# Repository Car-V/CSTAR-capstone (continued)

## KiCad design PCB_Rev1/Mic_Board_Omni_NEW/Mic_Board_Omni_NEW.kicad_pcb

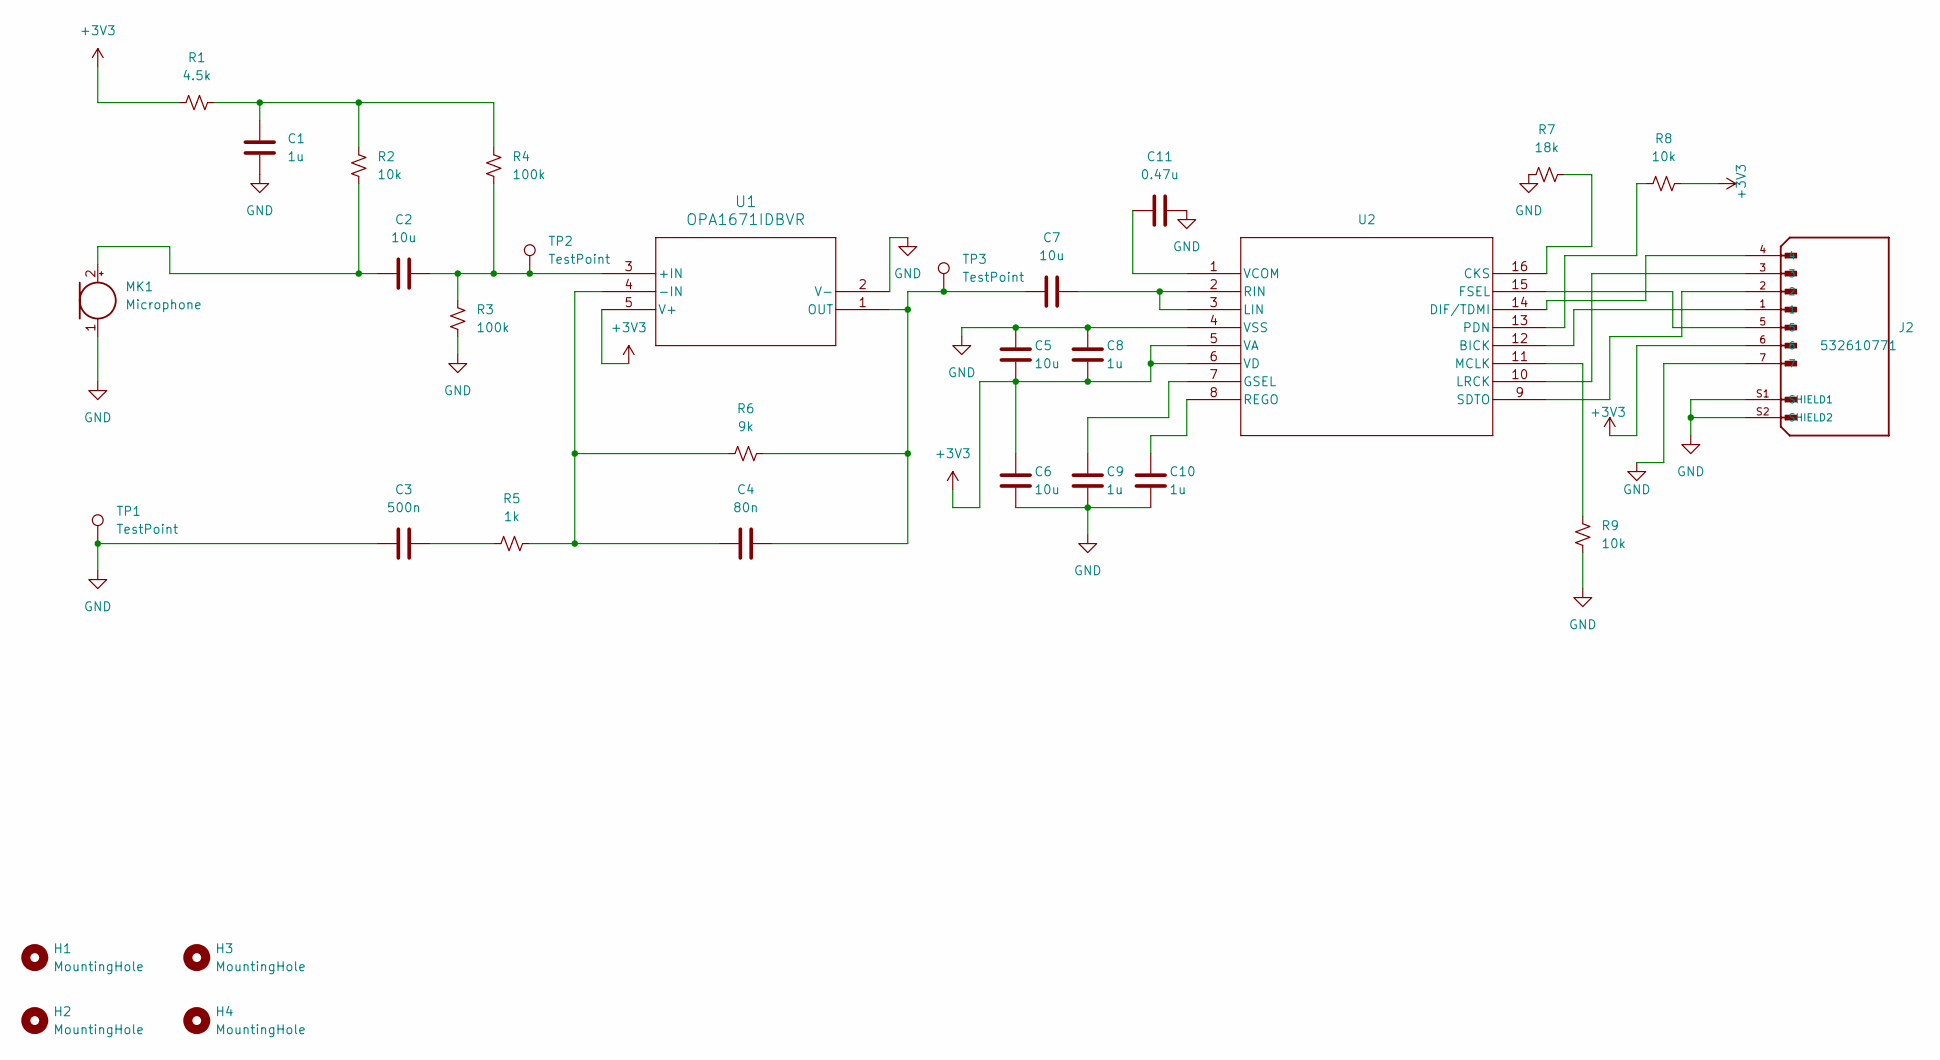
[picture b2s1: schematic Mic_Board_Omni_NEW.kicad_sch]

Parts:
C1, C8, C9, C10: 1u; C_0805_2012Metric; LCSC C519973
C2, C5, C6, C7: 10u; C_0805_2012Metric; LCSC C88484
C3: 500n; C_0805_2012Metric; LCSC C576434
C4: 80n; C_0805_2012Metric; LCSC C3857194
C11: 0.47u; C_0805_2012Metric; LCSC C519977
H1, H2, H3, H4: MountingHole; MountingHole_3.2mm_M3
J2: 532610771; MOLEX_connector; PARTREV J; DigiKey_Part_Number WM7625TR-ND
MK1: Microphone; Omnidirectional; LCSC C3273770
R1: 4.5k; R_0805_2012Metric; LCSC C865529
R2, R8, R9: 10k; R_0805_2012Metric; LCSC C110775
R3, R4: 100k; R_0805_2012Metric; LCSC C96346
R5: 1k; R_0805_2012Metric; LCSC C95781
R6: 9k; R_0805_2012Metric; LCSC C868262
R7: 18k; R_0805_2012Metric; LCSC C137468
TP1, TP2, TP3: TestPoint; TestPoint_Pad_D1.0mm
U1: OPA1671IDBVR; Op-Amp; LCSC C1849409
U2: ADC; LCSC C1519002

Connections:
+3V3: C5.2, C6.1, C8.2, J2.6, R1.2, R8.2, U1.5 (V+), U2.5 (VA), U2.6 (VD)
GND: C1.2, C3.1, C5.1, C6.2, C8.1, C9.2, C10.2, C11.2, H1.1, H2.1, H3.1, H4.1, J2.7, J2.S1 (SHIELD1), J2.S2 (SHIELD2), MK1.1 (-), R3.2, R7.1, R9.1, TP1.1, U1.2 (V-), U2.4 (VSS)
unnamed: C1.1, R1.1, R2.1, R4.1
unnamed: C3.2, R5.2
unnamed: C2.1, MK1.2 (+), R2.2
unnamed: C2.2, R3.1, R4.2, TP2.1, U1.3 (+IN)
unnamed: C4.1, R5.1, R6.2, U1.4 (-IN)
unnamed: C4.2, C7.1, R6.1, TP3.1, U1.1 (OUT)
unnamed: J2.1, U2.12 (BICK)
unnamed: R7.2, U2.16 (CKS)
unnamed: J2.4, U2.14 (DIF/TDMI)
unnamed: J2.5, U2.15 (FSEL)
unnamed: C9.1, U2.7 (GSEL)
unnamed: C7.2, U2.2 (RIN), U2.3 (LIN)
unnamed: J2.3, U2.10 (LRCK)
unnamed: R9.2, U2.11 (MCLK)
unnamed: R8.1, U2.13 (PDN)
unnamed: C10.1, U2.8 (REGO)
unnamed: J2.2, U2.9 (SDTO)
unnamed: C11.1, U2.1 (VCOM)

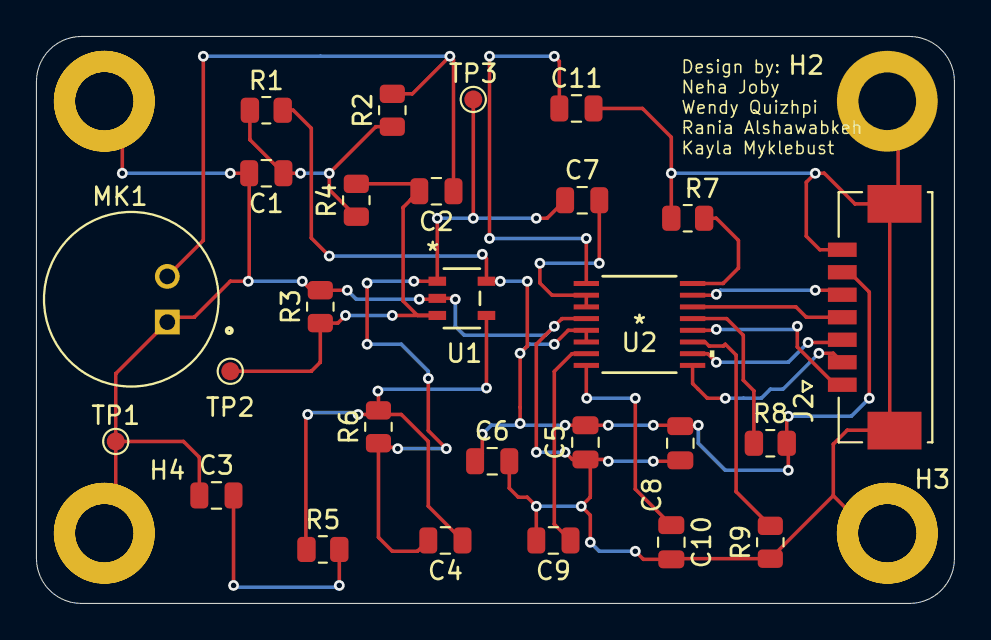
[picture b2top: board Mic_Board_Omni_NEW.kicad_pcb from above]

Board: 2 copper layers, 51.0 x 31.5 mm, 31 parts (0 on the bottom side), 20 nets.

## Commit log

2025-01-11 Add lifecycle_node package
2025-01-11 Moved test node to example sub_folder
2025-01-11 Add Subsystem Nodes
2025-01-11 Rename Folders
2025-01-11 Basic Object Oriented Setup
    This is super basic and I didn't put too much time into all the classes and stuff, will def need more and to iron out the purposes of each class. Lets discuss!
2025-01-12 Moving to CSTAR capstone
2025-01-12 Motor Driver
    Motor driver, encoder connections, and motor connections
2025-01-12 Wendy's Mic schem changes
2025-01-12 Both Mic Board 1 and Mic Board 2 were created + updated
2025-01-13 MicBoard Added to MainBoard
2025-01-14 Setup Software Layout
2025-01-14 Update Name
2025-01-14 Schem changes made in BMS
2025-01-14 LDO component files imported
2025-01-14 LDO footprint assigned
2025-01-14 Deleting PCB Layout
    errors in PCB layout
2025-01-15 Update Names
2025-01-15 Delete Lifecycle Manager for push to main
    Not yet certain on if this stuff is correct
2025-01-15 Bring Lifecycle Manager Back for Work on Branch
2025-01-15 All BMS footprints added
2025-01-15 I/O footprints added
2025-01-15 Op-Amp, OmiDirectional, ADC footnotes
2025-01-15 Header Connections FootPrint
2025-01-15 Footprints Update + Motor Drive Voltage Source Adjustments
2025-01-15 Footprints
2025-01-15 PCB Layout started
2025-01-15 Driver Schematic Update
    Vss / Vs and decoupling capacitor updates
2025-01-15 Audio schem file deleted
2025-01-15 Passives footprints changed
2025-01-15 RPi Connector Footprints
2025-01-15 Added new footprints
2025-01-15 more footprints changes
2025-01-15 diodes footprints added
2025-01-15 more footprints assigned
2025-01-15 FOOTPRINTS COMPLETE!!!!!
2025-01-15 Relative Path for FP Lib
2025-01-15 Maybe
2025-01-15 Some schem changes to BMS
2025-01-15 Revert "Maybe"
    This reverts commit 889b20bf1dc7f0bbf9995934c21d36586ef5963a.
2025-01-15 Some schem changes in I/O
2025-01-15 PCB maybe
2025-01-15 Micboard Omni PCB
2025-01-15 Edge cuts complete (borders + holes)
2025-01-16 board stackup complete
2025-01-16 moved some components
2025-01-16 more component changes
2025-01-16 Motor Drive Adjustment and Added Footprint for Polarized Cap
2025-01-16 BMS component org done
2025-01-16 Organized Motor Drive Components
2025-01-16 Power nets (local + global) created
2025-01-16 Renamed J1 Connector MicBoard
2025-01-16 mounting hole labeled
2025-01-16 Audio subsystem re-created
2025-01-16 audio file finalized
2025-01-16 Audio Back
2025-01-16 Revert "audio file finalized"
    This reverts commit 478d881cdb306273da0e0f1ea37dd6a2880d93a8.
2025-01-16 Revert "Audio subsystem re-created"
    This reverts commit 6dc47edf88eae56b01440ce5f2dfd5da155ce597.
2025-01-16 Reverting Audio Changes
2025-01-16 Updated Audio Schematic
2025-01-16 Added Footprints + Updated Layout for Audio Connectors
2025-01-16 Power nets updated in all schematics
2025-01-16 Connections to RPi GPIO Pins + Eliminating Errors from Layout
    Global net connections made from RPi GPIO pins.
    Error for mounting hole corrected -> mounting hole symbol imported into schematic and correct footprint assigned.
    Warnings for J10, J11, J12 connectors resolved- imported footprint for the connector from online (error in the one imported from KiCAD libraries with pins S1 and S2 labeled as MP in the footprint)
2025-01-17 Multiple Mounting Holes Added + GPIO Connections Added for RGB
2025-01-17 mounting holes set
2025-01-17 I/O component placement complete
2025-01-17 Lidar + Audio CP complete
2025-01-17 motor drive CP complete
2025-01-17 Power Update
2025-01-17 more CP changes
2025-01-17 more CP commits
2025-01-18 Component Placement complete
2025-01-18 Lidar routing complete
2025-01-18 routing attempt
2025-01-18 J12 connector routing
2025-01-18 Routing
2025-01-19 Added routing
2025-01-19 Revert "Audio Back"
    This reverts commit b4c952123ee183b7f2e3a0aacd1af0ad900a0b00.
2025-01-19 some more routing
2025-01-19 TP for Motor Drive + U2 Routing
2025-01-19 Routing U2 Enable Pin
2025-01-20 More routing
2025-01-20 Micboard pcb
2025-01-20 Mounting holes?
2025-01-20 accidently clicked
    hello
2025-01-21 Mic Board Mounting Hole Placement + Fillets + Eliminating Errors
    Placed mounting holes, added fillets to the corners of the pcb, and eliminated errors by using correct connector in place of the microphone in the schematic + layout
2025-01-21 mic board component adjustments
2025-01-21 traces
2025-01-21 Mic routing
2025-01-22 Ground Plane + Mic Board Adjustments
2025-01-22 some routing
2025-01-22 Micboard Done
2025-01-22 Uni Micboard
2025-01-22 Uni Delam Rev 1 Complete ?
2025-01-22 Mic board works!!
2025-01-22 main board routing
2025-01-22 Mainboard finished traces
2025-01-22 how do you polygon
2025-01-22 poly shit
2025-01-22 Errors
2025-01-22 added new power fet footprint
2025-01-22 fixed soldering bridge issue
2025-01-22 new power fet
2025-01-22 GND net to M5 holes
2025-01-22 another FET
2025-01-22 final touches... not rlly
2025-01-22 Added Old Footprint
2025-01-22 Updated Footprint + Symbol for FET
2025-01-22 Yay Kayla Fixed
    omg kayla youre so awsome thank you for saving us
2025-01-22 Grounded Mic Board Mounting Holes
2025-01-22 Mounting Hole Grounding
2025-01-22 Mic Board Setup Adjustments
2025-01-22 trace widths + teardrops
2025-01-22 some chanegufghjikjhg
2025-01-22 Mic Board Setup Changes
2025-01-22 Updates to routing
2025-01-22 deruioiygfhjik
2025-01-22 sOOOO many changes
2025-01-23 Trace width adjustments
2025-01-23 More routing/power planes
2025-01-23 Micboard Changes
2025-01-23 JLC ordering file created
2025-01-23 MicBoard silkscreen updated
2025-01-23 more MicBoard re-routing
2025-01-23 Mic Board silkscreen complete
2025-01-23 Main Board silkscreen changes
2025-01-24 Layout Basic Cleanup
2025-01-24 Sprinkled in GND vias
2025-01-24 Deleted massive PWR plane- need to add separate planes for each pwr rail
2025-01-24 New board potentially
2025-01-24 ESD Protection for USB Connector
2025-01-24 Fixed DRC errors
2025-01-24 Via sizes increased
2025-01-24 5V traces increased to 0.7mm
2025-01-24 12V traces widths increased 1.016
2025-01-24 Motor outputs traces were increased 1.016
2025-01-24 Motor Drive Implementation
    TO DO:
    - figure out full functionality and data flow with encoders and motors
    - test on rpi
    - check logic
2025-01-24 MICBOARD
2025-01-24 12V traces increased 2.54
2025-01-24 Name updates
    Just to distinguish between a motor direction versus the whole bot's direction
2025-01-24 PCB routing done
2025-01-24 New MIC Board UNI
2025-01-24 Updated GPIOs
2025-01-25 Audio Connector Pins
2025-01-25 connections for gpio and micboards
2025-01-25 Connections Adjustments
2025-01-26 Mic board updates
    Removing connector and attaching to J instead
2025-01-26 Removing lock
2025-01-26 Micboard Uni Complete
2025-01-26 New omni created
2025-01-26 Re Routing Rpi
2025-01-26 RPi Connections & Errors Corrected
2025-01-26 Friday Updates
2025-01-26 New again
2025-01-26 omni re 1
2025-01-26 Micboards DONE FINALLY
2025-01-26 new mic boards added
2025-01-26 Micboard Done with traces
2025-01-26 Running Motor Test
2025-01-26 UNI CSV DONE
2025-01-26 SAVE
2025-01-26 LCSC + CSV changes
2025-01-26 MICBOARD OMNI CSV DONE
2025-01-26 Centroid CSV for Main Board
2025-01-26 Micboard Centroid FIles DONE
2025-01-27 All gerber, BOM, + p&p files created
2025-01-29 Motor accel/decel, LiDAR beginnings
2025-01-29 Tested accel and decel
2025-01-29 Assumed that duty cycle of one motor will always match the other, cleanup
2025-01-29 Also made PWM_Hz static, see prev. commits if we want to make this members non-static
2025-02-02 Reading lidar data, with distance values, to file
2025-02-07 Baseline Audio Setup
2025-02-07 NEW ROS PACKAGES
2025-02-09 Bandpass Filter Function
2025-02-09 EVERYTHING ON THE RPI LOL
2025-02-10 Added input reading test case
2025-02-12 PID.py was created + Motor.py was updated w PID functions
2025-02-12 Updated Motor_Drive.py w PID
2025-02-12 Minor updates made to Motor_Drive_Manager.py
2025-02-12 Packet Manager
2025-02-14 LOGS ARE READABLE
2025-02-14 ACTUAL UPDATED LOGS
2025-02-19 begin adding odometry functions
2025-02-24 Creating Ros Script for odom
2025-02-24 Motor control test code completed
2025-03-10 MOTOR_testing
2025-03-11 Adjustments to audio testing with USB mic
2025-03-12 Created keyboard_controls.py
2025-03-12 GPIO PINS
2025-03-12 encoder files added
2025-03-12 Encoder.cpp and Encoder.h files updated to work w RPi
2025-03-12 encoder files updated
2025-03-14 Sending Audio Files Over Websocket
2025-03-17 Encoder testing updates
2025-03-23 odom?
2025-03-23 Today's live share updates
2025-03-23 Encoder Not Quaternion
2025-03-23 Quaternion
2025-03-23 update quat
2025-03-23 Edits to EncoderRos
2025-03-24 Working Encoder Node, need to test w GPIO
2025-03-28 basic rearranging
2025-03-30 updated pwm
2025-03-30 pwm 65
2025-03-30 pwm 60 50
2025-03-30 pwm 65 50
2025-03-30 pwm 65 45
2025-03-30 pwm 35 55
2025-03-30 pwm 55 40
2025-03-30 Filter Updates & Audio Manager Updates
2025-03-30 pwm 30 45
2025-03-30 pwm 30 40
2025-03-30 Updated GPIO
2025-03-30 Delam Detection
2025-03-30 encoder stuff
2025-03-31 test
2025-03-31 Basic
    random testing changes
2025-03-31 calc distance edit
2025-03-31 ommit
2025-03-31 odometry update
    dis bish
2025-03-31 main
2025-03-31 setting up pid
2025-03-31 changed calc
2025-04-01 some changes
2025-04-01 pushing
2025-04-02 last push
2025-04-02 removing record function that isn't necessary
2025-04-02 comment out audio
2025-04-02 change
2025-04-02 duty cycle
2025-04-02 audio
2025-04-03 avg_mag to just mag (summing magnitudes)
2025-04-03 audio manager function for ROS integration
2025-04-14 Added audio driver attempt and test scripts
